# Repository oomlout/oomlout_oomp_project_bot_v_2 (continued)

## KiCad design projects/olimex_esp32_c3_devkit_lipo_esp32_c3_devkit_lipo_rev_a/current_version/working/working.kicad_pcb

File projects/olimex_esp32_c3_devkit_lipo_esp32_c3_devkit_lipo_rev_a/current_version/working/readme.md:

# esp32_c3_devkit_lipo
 
## summary 
* id: olimex_esp32_c3_devkit_lipo_esp32_c3_devkit_lipo_rev_a
* user: olimex
* name: esp32_c3_devkit_lipo
* board: esp32_c3_devkit_lipo_rev_a
* repo: https://github.com/OLIMEX/ESP32-C3-DevKit-Lipo
* src_file_repo_kicad_pcb: HARDWARE/ESP32-C3-DevKit-Lipo_Rev_A/ESP32-C3-DevKit-Lipo_Rev_A.kicad_pcb
* src_file_repo_kicad_pcb_link: https://github.com/OLIMEX/ESP32-C3-DevKit-Lipo/tree/main/HARDWARE/ESP32-C3-DevKit-Lipo_Rev_A/ESP32-C3-DevKit-Lipo_Rev_A.kicad_pcb

* src_file_repo_sch: HARDWARE/ESP32-C3-DevKit-Lipo_Rev_A/ESP32-C3-DevKit-Lipo_Rev_A.sch
* src_file_repo_sch_link: https://github.com/OLIMEX/ESP32-C3-DevKit-Lipo/tree/main/HARDWARE/ESP32-C3-DevKit-Lipo_Rev_A/ESP32-C3-DevKit-Lipo_Rev_A.sch
* full details link: https://github.com/oomlout/oomlout_oomp_project_bot_v_2/tree/main/projects/olimex_esp32_c3_devkit_lipo_esp32_c3_devkit_lipo_rev_a/current_version/working

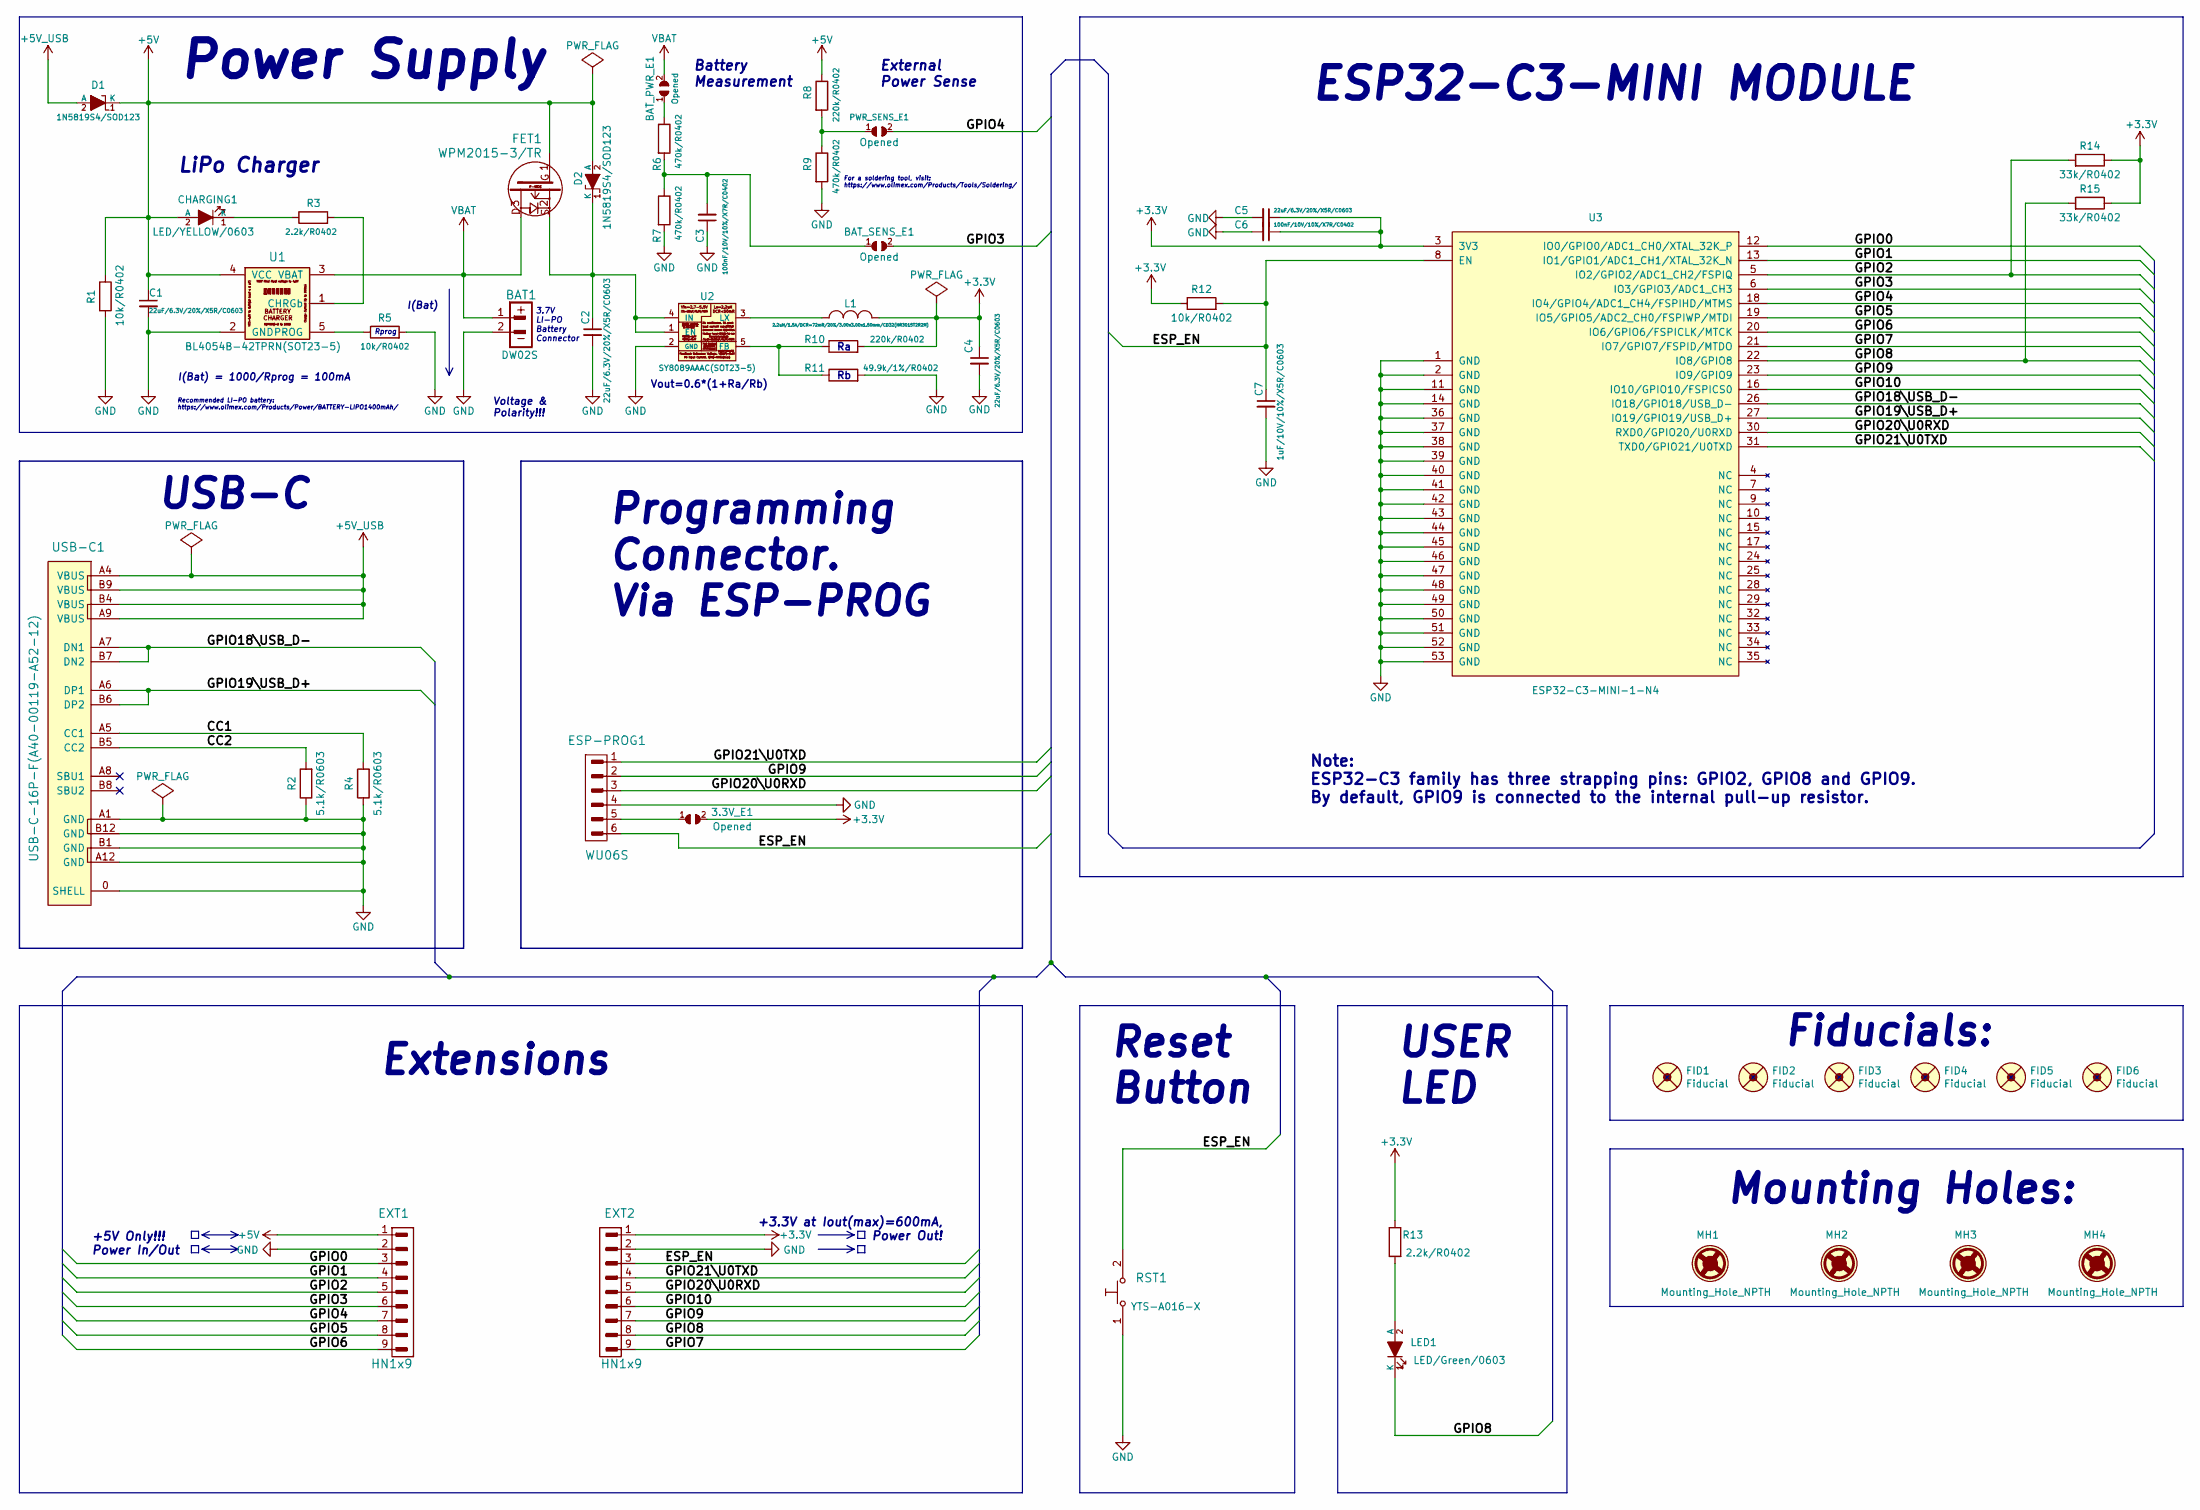
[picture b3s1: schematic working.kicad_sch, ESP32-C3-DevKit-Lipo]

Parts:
3.3V_E1: Opened; SJ_1_SMALLER
BAT1: DW02S; LIPO_BAT_VERTICAL_DW02S
BAT_PWR_E1: Opened; SJ_1_SMALLER
BAT_SENS_E1: Opened; SJ_1_SMALLER
C1, C2, C4, C5: 22uF/6.3V/20%/X5R/C0603; C_0603_5MIL_DWS
C3, C6: 100nF/10V/10%/X7R/C0402; C_0402_5MIL_DWS
C7: 1uF/10V/10%/X5R/C0603; C_0603_5MIL_DWS
CHARGING1: LED/YELLOW/0603; LED_0603_KA
D1, D2: 1N5819S4/SOD123; SOD-123_1C-2A_KA
ESP-PROG1: WU06S
EXT1, EXT2: HN1x9
FET1: WPM2015-3/TR; SOT23
FID1, FID2, FID3, FID4, FID5, FID6: Fiducial; Fiducial1x3
L1: 2.2uH/1.5A/DCR=72mR/20%/3.00x3.00x1.50mm/CD32(NR3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; CD32
LED1: LED/Green/0603; LED_0603_KA
MH1, MH2, MH3, MH4: Mounting_Hole_NPTH; Mounting_Hole_Drill-3.3mm_Clerance-7mm
PWR_SENS_E1: Opened; SJ_1_SMALLER
R1, R5, R12: 10k/R0402; R_0402_5MIL_DWS
R2, R4: 5.1k/R0603; R_0603_5MIL_DWS
R3, R13: 2.2k/R0402; R_0402_5MIL_DWS
R6, R7, R9: 470k/R0402; R_0402_5MIL_DWS
R8, R10: 220k/R0402; R_0402_5MIL_DWS
R11: 49.9k/1%/R0402; R_0402_5MIL_DWS
R14, R15: 33k/R0402; R_0402_5MIL_DWS
RST1: YTS-A016-X
U1: BL4054B-42TPRN(SOT23-5); SOT-23-5
U2: SY8089AAAC(SOT23-5); SOT-23-5
U3: ESP32-C3-MINI-1-N4; ESP32-­C3-­MINI­-1
USB-C1: USB-C-16P-F(A40-00119-A52-12); USB2.0_TYPE-C(A40-00119-A52-12)

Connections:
+3V3: 3.3V_E1.2, C4.1, C5.1, C6.1, EXT2.1, L1.2, R10.2, R12.1, R13.1, R14.1, R15.1, U3.3 (3V3)
+5V: C1.1, CHARGING1.2 (A), D1.1 (K), D2.2 (A), EXT1.1, FET1.1, R1.1, R8.1, U1.4 (VCC)
+5V_USB: D1.2 (A), USB-C1.A4 (VBUS), USB-C1.A9 (VBUS), USB-C1.B4 (VBUS), USB-C1.B9 (VBUS)
/CC1: R4.2, USB-C1.A5 (CC1)
/CC2: R2.2, USB-C1.B5 (CC2)
/ESP_EN: C7.1, ESP-PROG1.6, EXT2.3, R12.2, RST1.2, U3.8 (EN)
/GPIO0: EXT1.3, U3.12 (IO0/GPIO0/ADC1_CH0/XTAL_32K_P)
/GPIO1: EXT1.4, U3.13 (IO1/GPIO1/ADC1_CH1/XTAL_32K_N)
/GPIO2: EXT1.5, R14.2, U3.5 (IO2/GPIO2/ADC1_CH2/FSPIQ)
/GPIO3: BAT_SENS_E1.2, EXT1.6, U3.6 (IO3/GPIO3/ADC1_CH3)
/GPIO4: EXT1.7, PWR_SENS_E1.2, U3.18 (IO4/GPIO4/ADC1_CH4/FSPIHD/MTMS)
/GPIO5: EXT1.8, U3.19 (IO5/GPIO5/ADC2_CH0/FSPIWP/MTDI)
/GPIO6: EXT1.9, U3.20 (IO6/GPIO6/FSPICLK/MTCK)
/GPIO7: EXT2.9, U3.21 (IO7/GPIO7/FSPID/MTDO)
/GPIO8: EXT2.8, LED1.1 (K), R15.2, U3.22 (IO8/GPIO8)
/GPIO9: ESP-PROG1.2, EXT2.7, U3.23 (IO9/GPIO9)
/GPIO10: EXT2.6, U3.16 (IO10/GPIO10/FSPICS0)
/GPIO18\USB_D-: U3.26 (IO18/GPIO18/USB_D-), USB-C1.A7 (DN1), USB-C1.B7 (DN2)
/GPIO19\USB_D+: U3.27 (IO19/GPIO19/USB_D+), USB-C1.A6 (DP1), USB-C1.B6 (DP2)
/GPIO20\U0RXD: ESP-PROG1.3, EXT2.5, U3.30 (RXD0/GPIO20/U0RXD)
/GPIO21\U0TXD: ESP-PROG1.1, EXT2.4, U3.31 (TXD0/GPIO21/U0TXD)
GND: BAT1.2, C1.2, C2.2, C3.1, C4.2, C5.2, C6.2, C7.2, ESP-PROG1.4, EXT1.2, EXT2.2, R1.2, R2.1, R4.1, R5.2, R7.2, R9.2, R11.2, RST1.1, U1.2 (GND), U2.2 (GND), U3.1 (GND), U3.2 (GND), U3.11 (GND), U3.14 (GND), U3.36 (GND), U3.37 (GND), U3.38 (GND), U3.39 (GND), U3.40 (GND), U3.41 (GND), U3.42 (GND), U3.43 (GND), U3.44 (GND), U3.45 (GND), U3.46 (GND), U3.47 (GND), U3.48 (GND), U3.49 (GND), U3.50 (GND), U3.51 (GND), U3.52 (GND), U3.53 (GND), USB-C1.0 (SHELL), USB-C1.A1 (GND), USB-C1.A12 (GND), USB-C1.B1 (GND), USB-C1.B12 (GND)
unnamed: 3.3V_E1.1, ESP-PROG1.5
unnamed: BAT_PWR_E1.1, R6.1
unnamed: BAT_SENS_E1.1, C3.2, R6.2, R7.1
unnamed: C2.1, D2.1 (K), FET1.2, U2.1 (EN), U2.4 (IN)
unnamed: CHARGING1.1 (K), R3.1
unnamed: L1.1, U2.3 (LX)
unnamed: LED1.2 (A), R13.2
unnamed: PWR_SENS_E1.1, R8.2, R9.1
unnamed: R3.2, U1.1 (CHRGb)
unnamed: R5.1, U1.5 (PROG)
unnamed: R10.1, R11.1, U2.5 (FB)
VBAT: BAT1.1, BAT_PWR_E1.2, FET1.3, U1.3 (VBAT)

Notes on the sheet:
I(Bat)
Note: ESP32-C3 family has three strapping pins: GPIO2, GPIO8 and GPIO9. By default, GPIO9 is connected to the internal pull-up resistor.
Fiducials:
Battery Measurement
Power Supply
External Power Sense
LiPo Charger
Programming Connector. Via ESP-PROG
Mounting Holes:
+3.3V at Iout(max)=600mA, Power Out!
+5V Only!!! Power In/Out
Extensions
Reset Button
USER LED
ESP32-C3-MINI MODULE
Vout=0.6*(1+Ra/Rb)
Voltage & Polarity!!!
I(Bat) = 1000/Rprog = 100mA
Recommended LI-PO battery: https://www.olimex.com/Products/Power/BATTERY-LIPO1400mAh/
For a soldering tool, visit: https://www.olimex.com/Products/Tools/Soldering/
3.7V LI-PO Battery Connector
USB-C
Rprog

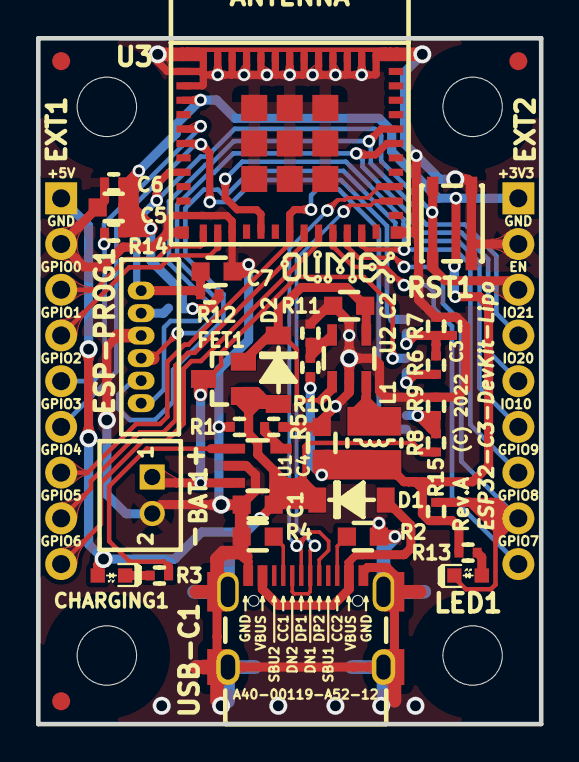
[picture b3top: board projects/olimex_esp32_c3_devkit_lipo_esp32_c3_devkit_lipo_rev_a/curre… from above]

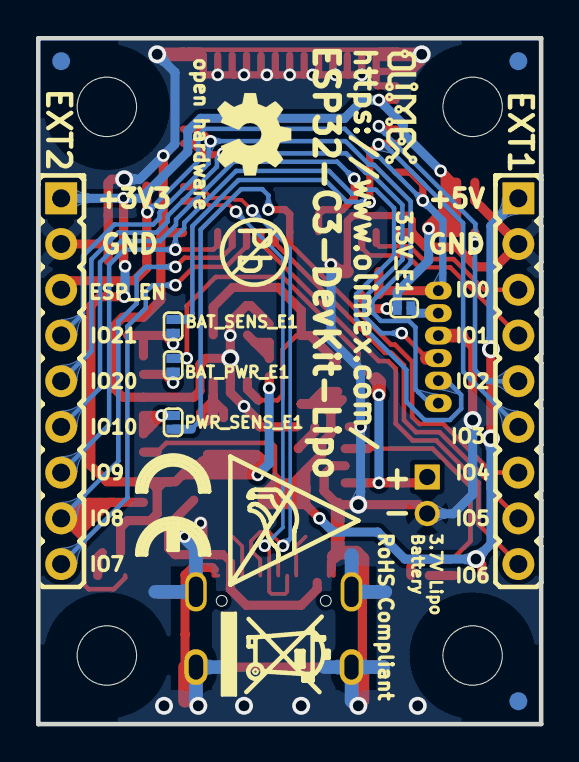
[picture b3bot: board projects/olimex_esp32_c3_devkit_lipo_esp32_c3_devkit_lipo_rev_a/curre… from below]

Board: 2 copper layers, 27.9 x 38.1 mm, 58 parts (15 on the bottom side), 34 nets.

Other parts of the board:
Logo_OLIMEX_1: Logo_OLIMEX_1; Logo_OLIMEX_80
Logo_OLIMEX_2: Logo_OLIMEX_2; Logo_OLIMEX_80
Sign_Antistatic: Sign_Antistatic
Sign_CE: CE_Sign
Sign_OSHW_7.3x6.0mm: Sign_OSHW_7.3x6.0mm; Sign_OSHW_7.3x6.0mmn
Sign_PB-Free: Sign_PB-Free
Sign_RecycleBin_1: Sign_RecycleBin_1

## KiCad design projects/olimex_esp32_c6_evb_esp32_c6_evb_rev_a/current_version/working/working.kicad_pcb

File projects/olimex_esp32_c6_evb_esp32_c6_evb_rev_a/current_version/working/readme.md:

# esp32_c6_evb
 
## summary 
* id: olimex_esp32_c6_evb_esp32_c6_evb_rev_a
* user: olimex
* name: esp32_c6_evb
* board: esp32_c6_evb_rev_a
* repo: https://github.com/OLIMEX/ESP32-C6-EVB
* src_file_repo_kicad_pcb: HARDWARE/Hardware-revision-A/ESP32-C6-EVB_Rev_A.kicad_pcb
* src_file_repo_kicad_pcb_link: https://github.com/OLIMEX/ESP32-C6-EVB/tree/main/HARDWARE/Hardware-revision-A/ESP32-C6-EVB_Rev_A.kicad_pcb

* src_file_repo_sch: HARDWARE/Hardware-revision-A/ESP32-C6-EVB_Rev_A.sch
* src_file_repo_sch_link: https://github.com/OLIMEX/ESP32-C6-EVB/tree/main/HARDWARE/Hardware-revision-A/ESP32-C6-EVB_Rev_A.sch
* full details link: https://github.com/oomlout/oomlout_oomp_project_bot_v_2/tree/main/projects/olimex_esp32_c6_evb_esp32_c6_evb_rev_a/current_version/working

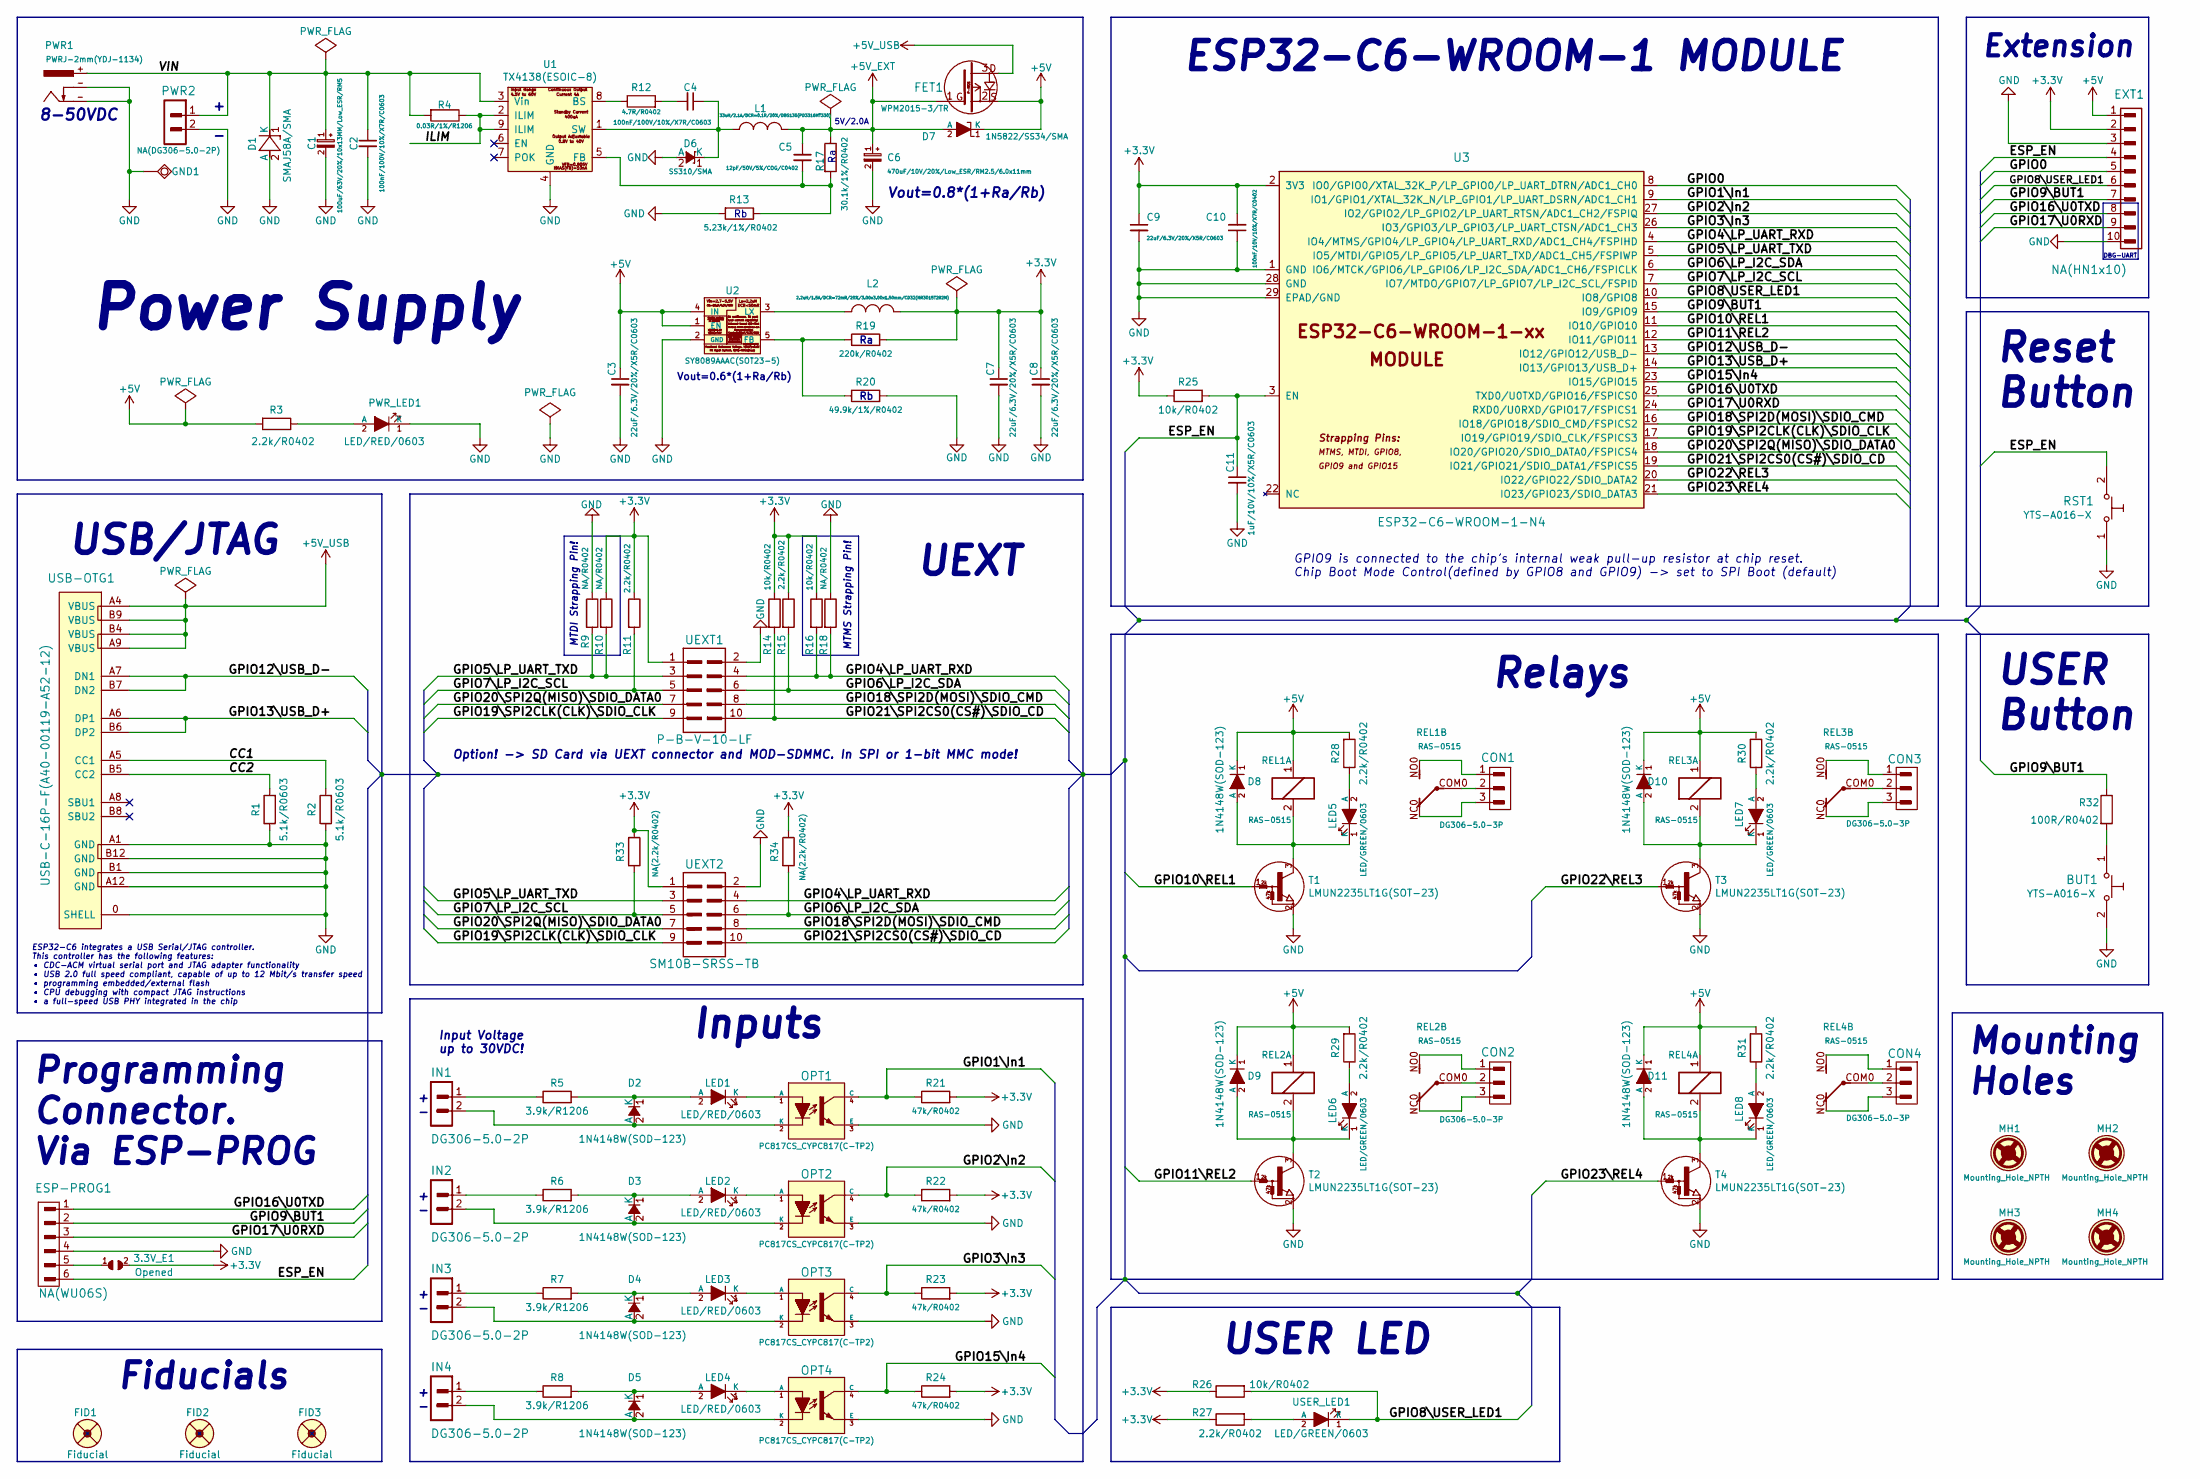
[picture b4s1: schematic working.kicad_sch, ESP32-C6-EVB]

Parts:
3.3V_E1: Opened; SJ_1_SMALLER
BUT1: YTS-A016-X
C1: 100uF/63V/20%/10x13MM/Low_ESR/RM5; CPOL-RM5mm_10.0x16.0mm_PTH
C2, C4: 100nF/100V/10%/X7R/C0603; C_0603_5MIL_DWS
C3, C7, C8, C9: 22uF/6.3V/20%/X5R/C0603; C_0603_5MIL_DWS
C5: 12pF/50V/5%/COG/C0402; C_0402_5MIL_DWS
C6: 470uF/10V/20%/Low_ESR/RM2.5/6.0x11mm; CPOL-RM2.5mm_6.3x11mm_PTH
C10: 100nF/10V/10%/X7R/C0402; C_0402_5MIL_DWS
C11: 1uF/10V/10%/X5R/C0603; C_0603_5MIL_DWS
CON1, CON2, CON3, CON4: DG306-5.0-3P; TB3-DG306-5.0_3P
D1: SMAJ58A/SMA; SMA-KA
D2, D3, D4, D5, D8, D9, D10, D11: 1N4148W(SOD-123); SOD-123_1C-2A_KA
D6: SS310/SMA; SMA-KA
D7: 1N5822/SS34/SMA; SMA-KA
ESP-PROG1: NA(WU06S); WU06S
EXT1: NA(HN1x10); HN1x10
FET1: WPM2015-3/TR; SOT23
FID1, FID2, FID3: Fiducial; Fiducial1x3
GND1: TESTPAD; TEST_PAD40x70_SQUARE
IN1, IN2, IN3, IN4: DG306-5.0-2P; TB2-DG306-5.0_2P
L1: 33uH/2.1A/DCR=0.1R/20%/DBS135(PD3316MT330); DBS135
L2: 2.2uH/1.5A/DCR=72mR/20%/3.00x3.00x1.50mm/CD32(NR3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; CD32
LED1, LED2, LED3, LED4: LED/RED/0603; LED_0603_KA
LED5, LED6, LED7, LED8: LED/GREEN/0603; LED_0603_KA
MH1, MH2, MH3, MH4: Mounting_Hole_NPTH; Mounting_Hole_Drill-3.3mm_Clerance-7mm
OPT1, OPT2, OPT3, OPT4: PC817CS_CYPC817(C-TP2); H11A817C_SMD(PC817X3NIP06)_FP
PWR1: PWRJ-2mm(YDJ-1134); PWRJ-2mm(YDJ-1136)
PWR2: NA(DG306-5.0-2P); TB2-DG306-5.0_2P
PWR_LED1: LED/RED/0603; LED_0603_KA
R1, R2: 5.1k/R0603; R_0603_5MIL_DWS
R3, R11, R15, R27, R28, R29, R30, R31: 2.2k/R0402; R_0402_5MIL_DWS
R4: 0.03R/1%/R1206; R_1206_5MIL_DWS
R5, R6, R7, R8: 3.9k/R1206; R_1206_5MIL_DWS
R9, R10, R18: NA/R0402; R_0402_5MIL_DWS
R12: 4.7R/R0402; R_0402_5MIL_DWS
R13: 5.23k/1%/R0402; R_0402_5MIL_DWS
R14, R16, R25, R26: 10k/R0402; R_0402_5MIL_DWS
R17: 30.1k/1%/R0402; R_0402_5MIL_DWS
R19: 220k/R0402; R_0402_5MIL_DWS
R20: 49.9k/1%/R0402; R_0402_5MIL_DWS
R21, R22, R23, R24: 47k/R0402; R_0402_5MIL_DWS
R32: 100R/R0402; R_0402_5MIL_DWS
R33, R34: NA(2.2k/R0402); R_0402_5MIL_DWS
REL1, REL2, REL3, REL4: RAS-0515; Relay_RAS-05-15
RST1: YTS-A016-X
T1, T2, T3, T4: LMUN2235LT1G(SOT-23); SOT23
U1: TX4138(ESOIC-8); ESOIC-8
U2: SY8089AAAC(SOT23-5); SOT-23-5
U3: ESP32-C6-WROOM-1-N4; ESP32-C6-WROOM-1-xx-UNIVERSAL_MODULE
UEXT1: P-B-V-10-LF; GBH-254-SMT-10
UEXT2: SM10B-SRSS-TB
USB-OTG1: USB-C-16P-F(A40-00119-A52-12); USB2.0_TYPE-C(A40-00119-A52-12)
USER_LED1: LED/GREEN/0603; LED_0603_KA

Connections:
+3.3V: 3.3V_E1.2, C7.1, C8.1, C9.1, C10.2, EXT1.2, L2.2, R10.1, R11.1, R14.1, R15.1, R16.1, R19.2, R21.2, R22.2, R23.2, R24.2, R25.1, R26.1, R27.1, R33.1, R34.1, U3.2 (3V3), UEXT1.1, UEXT2.1
+5V: C3.1, D7.1 (K), D8.1 (K), D9.1 (K), D10.1 (K), D11.1 (K), EXT1.1, FET1.2, R3.2, R28.2, R29.2, R30.2, R31.2, REL1.1, REL2.1, REL3.1, REL4.1, U2.1 (EN), U2.4 (IN)
+5V_EXT: C5.1, C6.1 (+), D7.2 (A), FET1.1, L1.2, R17.1
+5V_USB: FET1.3, USB-OTG1.A4 (VBUS), USB-OTG1.A9 (VBUS), USB-OTG1.B4 (VBUS), USB-OTG1.B9 (VBUS)
/CC1: R2.2, USB-OTG1.A5 (CC1)
/CC2: R1.2, USB-OTG1.B5 (CC2)
/ESP_EN: C11.1, ESP-PROG1.6, EXT1.4, R25.2, RST1.2, U3.3 (EN)
/GPIO0: EXT1.5, U3.8 (IO0/GPIO0/XTAL_32K_P/LP_GPIO0/LP_UART_D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)
/GPIO1\In1: OPT1.4 (C), R21.1, U3.9 (IO1/GPIO1/XTAL_32K_N/LP_GPIO1/LP_UART_D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)
/GPIO2\In2: OPT2.4 (C), R22.1, U3.27 (IO2/GPIO2/LP_GPIO2/LP_UART_RTSN/ADC1_CH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)
/GPIO3\In3: OPT3.4 (C), R23.1, U3.26 (IO3/GPIO3/LP_GPIO3/LP_UART_CTSN/ADC1_CH3)
/GPIO4\LP_UART_RXD: R16.2, R18.2, U3.4 (IO4/MTMS/GPIO4/LP_GPIO4/LP_UART_RXD/ADC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), UEXT1.4, UEXT2.4
/GPIO5\LP_UART_TXD: R9.2, R10.2, U3.5 (IO5/MTDI/GPIO5/LP_GPIO5/LP_UART_TXD/ADC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), UEXT1.3, UEXT2.3
/GPIO6\LP_I2C_SDA: R15.2, R34.2, U3.6 (IO6/MTCK/GPIO6/LP_GPIO6/LP_I2C_SDA/ADC1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), UEXT1.6, UEXT2.6
/GPIO7\LP_I2C_SCL: R11.2, R33.2, U3.7 (IO7/MTDO/GPIO7/LP_GPIO7/LP_I2C_SCL/FSPID), UEXT1.5, UEXT2.5
/GPIO8\USER_LED1: EXT1.6, R26.2, U3.10 (IO8/GPIO8), USER_LED1.1 (K)
/GPIO9\BUT1: ESP-PROG1.2, EXT1.7, R32.1, U3.15 (IO9/GPIO9)
/GPIO10\REL1: T1.1 (B), U3.11 (IO10/GPIO10)
/GPIO11\REL2: T2.1 (B), U3.12 (IO11/GPIO11)
/GPIO12\USB_D-: U3.13 (IO12/GPIO12/USB_D-), USB-OTG1.A7 (DN1), USB-OTG1.B7 (DN2)
/GPIO13\USB_D+: U3.14 (IO13/GPIO13/USB_D+), USB-OTG1.A6 (DP1), USB-OTG1.B6 (DP2)
/GPIO15\In4: OPT4.4 (C), R24.1, U3.23 (IO15/GPIO15)
/GPIO16\U0TXD: ESP-PROG1.1, EXT1.8, U3.25 (TXD0/U0TXD/GPIO16/FSPICS0)
/GPIO17\U0RXD: ESP-PROG1.3, EXT1.9, U3.24 (RXD0/U0RXD/GPIO17/FSPICS1)
/GPIO18\SPI2D(MOSI)\SDIO_CMD: U3.16 (IO18/GPIO18/SDIO_CMD/FSPICS2), UEXT1.8, UEXT2.8
/GPIO19\SPI2CLK(CLK)\SDIO_CLK: U3.17 (IO19/GPIO19/SDIO_CLK/FSPICS3), UEXT1.9, UEXT2.9
/GPIO20\SPI2Q(MISO)\SDIO_DATA0: U3.18 (IO20/GPIO20/SDIO_DATA0/FSPICS4), UEXT1.7, UEXT2.7
/GPIO21\SPI2CS0(CS#)\SDIO_CD: R14.2, U3.19 (IO21/GPIO21/SDIO_DATA1/FSPICS5), UEXT1.10, UEXT2.10
/GPIO22\REL3: T3.1 (B), U3.20 (IO22/GPIO22/SDIO_DATA2)
/GPIO23\REL4: T4.1 (B), U3.21 (IO23/GPIO23/SDIO_DATA3)
/ILIM: R4.1, U1.2 (ILIM), U1.9 (ILIM)
/VIN: C1.1 (+), C2.1, D1.1 (K), PWR1.+, PWR2.1, R4.2, U1.3 (Vin)
GND: BUT1.2, C1.2 (-), C2.2, C3.2, C6.2 (-), C7.2, C8.2, C9.2, C10.1, C11.2, D1.2 (A), D6.2 (A), ESP-PROG1.4, EXT1.3, EXT1.10, GND1.1, OPT1.3 (E), OPT2.3 (E), OPT3.3 (E), OPT4.3 (E), PWR1.-, PWR2.2, PWR_LED1.1 (K), R1.1, R2.1, R9.1, R13.2, R18.1, R20.2, RST1.1, T1.2 (E), T2.2 (E), T3.2 (E), T4.2 (E), U1.4 (GND), U2.2 (GND), U3.1 (GND), U3.28 (GND), U3.29 (EPAD/GND), UEXT1.2, UEXT2.2, USB-OTG1.0 (SHELL), USB-OTG1.A1 (GND), USB-OTG1.A12 (GND), USB-OTG1.B1 (GND), USB-OTG1.B12 (GND)
unnamed: 3.3V_E1.1, ESP-PROG1.5
unnamed: BUT1.1, R32.2
unnamed: C4.1, D6.1 (K), L1.1, U1.1 (SW)
unnamed: C4.2, R12.2
unnamed: C5.2, R13.1, R17.2, U1.5 (FB)
unnamed: CON1.1, REL1.NO0
unnamed: CON1.2, REL1.COM0
unnamed: CON1.3, REL1.NC0
unnamed: CON2.1, REL2.NO0
unnamed: CON2.2, REL2.COM0
unnamed: CON2.3, REL2.NC0
unnamed: CON3.1, REL3.NO0
unnamed: CON3.2, REL3.COM0
unnamed: CON3.3, REL3.NC0
unnamed: CON4.1, REL4.NO0
unnamed: CON4.2, REL4.COM0
unnamed: CON4.3, REL4.NC0
unnamed: D2.1 (K), LED1.2 (A), R5.2
unnamed: D2.2 (A), IN1.2, OPT1.2 (K)
unnamed: D3.1 (K), LED2.2 (A), R6.2
unnamed: D3.2 (A), IN2.2, OPT2.2 (K)
unnamed: D4.1 (K), LED3.2 (A), R7.2
unnamed: D4.2 (A), IN3.2, OPT3.2 (K)
unnamed: D5.1 (K), LED4.2 (A), R8.2
unnamed: D5.2 (A), IN4.2, OPT4.2 (K)
unnamed: D8.2 (A), LED5.1 (K), REL1.2, T1.3 (C)
unnamed: D9.2 (A), LED6.1 (K), REL2.2, T2.3 (C)
unnamed: D10.2 (A), LED7.1 (K), REL3.2, T3.3 (C)
unnamed: D11.2 (A), LED8.1 (K), REL4.2, T4.3 (C)
unnamed: IN1.1, R5.1
unnamed: IN2.1, R6.1
unnamed: IN3.1, R7.1
unnamed: IN4.1, R8.1
unnamed: L2.1, U2.3 (LX)
unnamed: LED1.1 (K), OPT1.1 (A)
unnamed: LED2.1 (K), OPT2.1 (A)
unnamed: LED3.1 (K), OPT3.1 (A)
unnamed: LED4.1 (K), OPT4.1 (A)
unnamed: LED5.2 (A), R28.1
unnamed: LED6.2 (A), R29.1
unnamed: LED7.2 (A), R30.1
unnamed: LED8.2 (A), R31.1
unnamed: PWR_LED1.2 (A), R3.1
unnamed: R12.1, U1.8 (BS)
unnamed: R19.1, R20.1, U2.5 (FB)
unnamed: R27.2, USER_LED1.2 (A)

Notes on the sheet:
MTMS Strapping Pin!
Reset Button
Power Supply
Input Voltage up to 30VDC!
Relays
GPIO9 is connected to the chip’s internal weak pull-up resistor at chip reset. Chip Boot Mode Control(defined by GPIO8 and GPIO9) -> set to SPI Boot (default)
USER Button
5V/2.0A
UEXT
Extension
Inputs
8-50VDC
Vout=0.8*(1+Ra/Rb)
USB/JTAG
Vout=0.6*(1+Ra/Rb)
Fiducials
USER LED
DBG-UART
ESP32-C6 integrates a USB Serial/JTAG controller. This controller has the following features: • CDC-ACM virtual serial port and JTAG adapter functionality • USB 2.0 full speed compliant, capable of up to 12 Mbit/s transfer speed • programming embedded/external flash • CPU debugging with compact JTA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
Programming Connector. Via ESP-PROG
ESP32-C6-WROOM-1 MODULE
Mounting Holes
Option! -> SD Card via UEXT connector and MOD-SDMMC. In SPI or 1-bit MMC mode!
MTDI Strapping Pin!

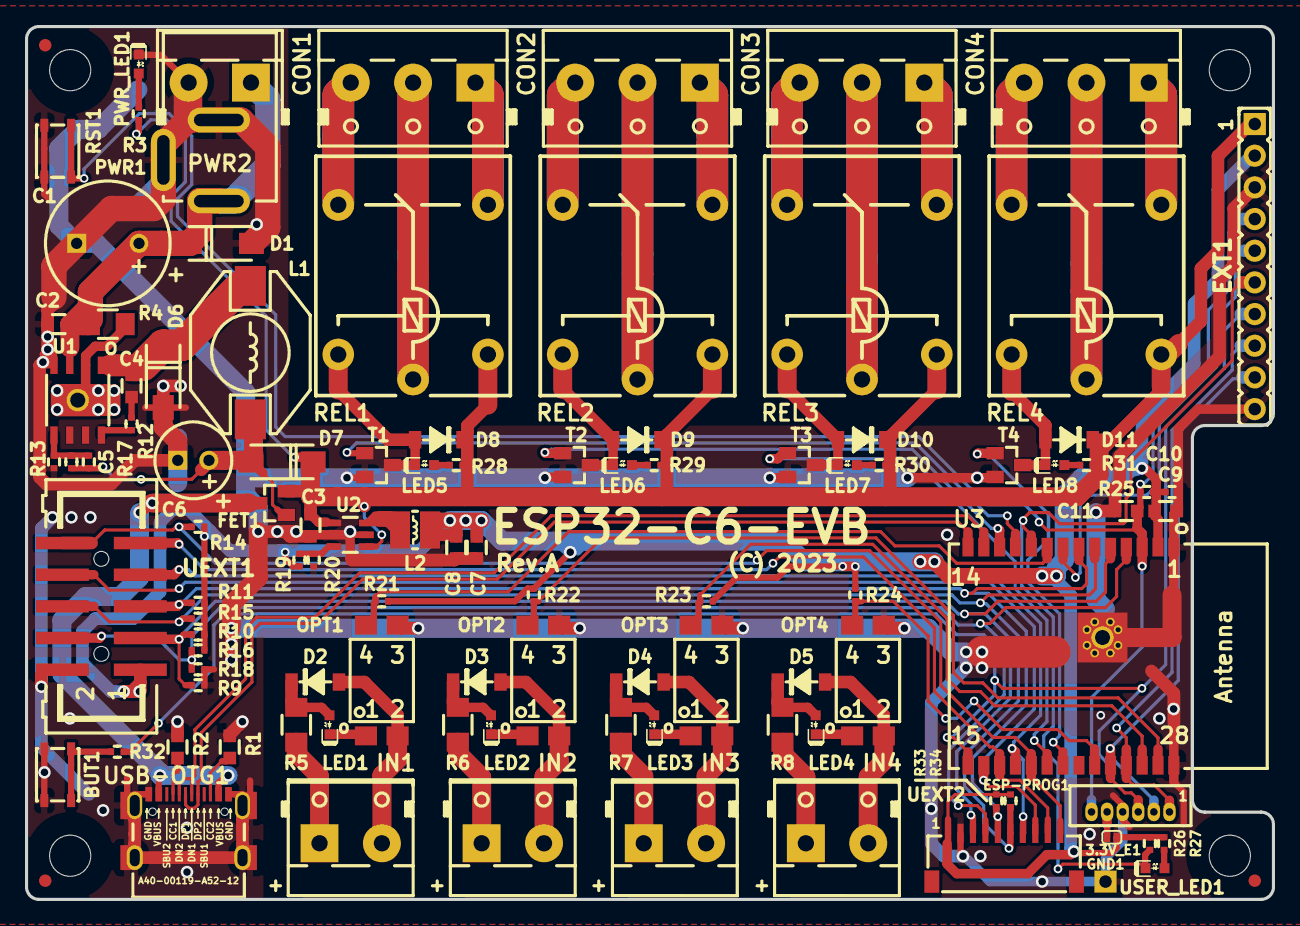
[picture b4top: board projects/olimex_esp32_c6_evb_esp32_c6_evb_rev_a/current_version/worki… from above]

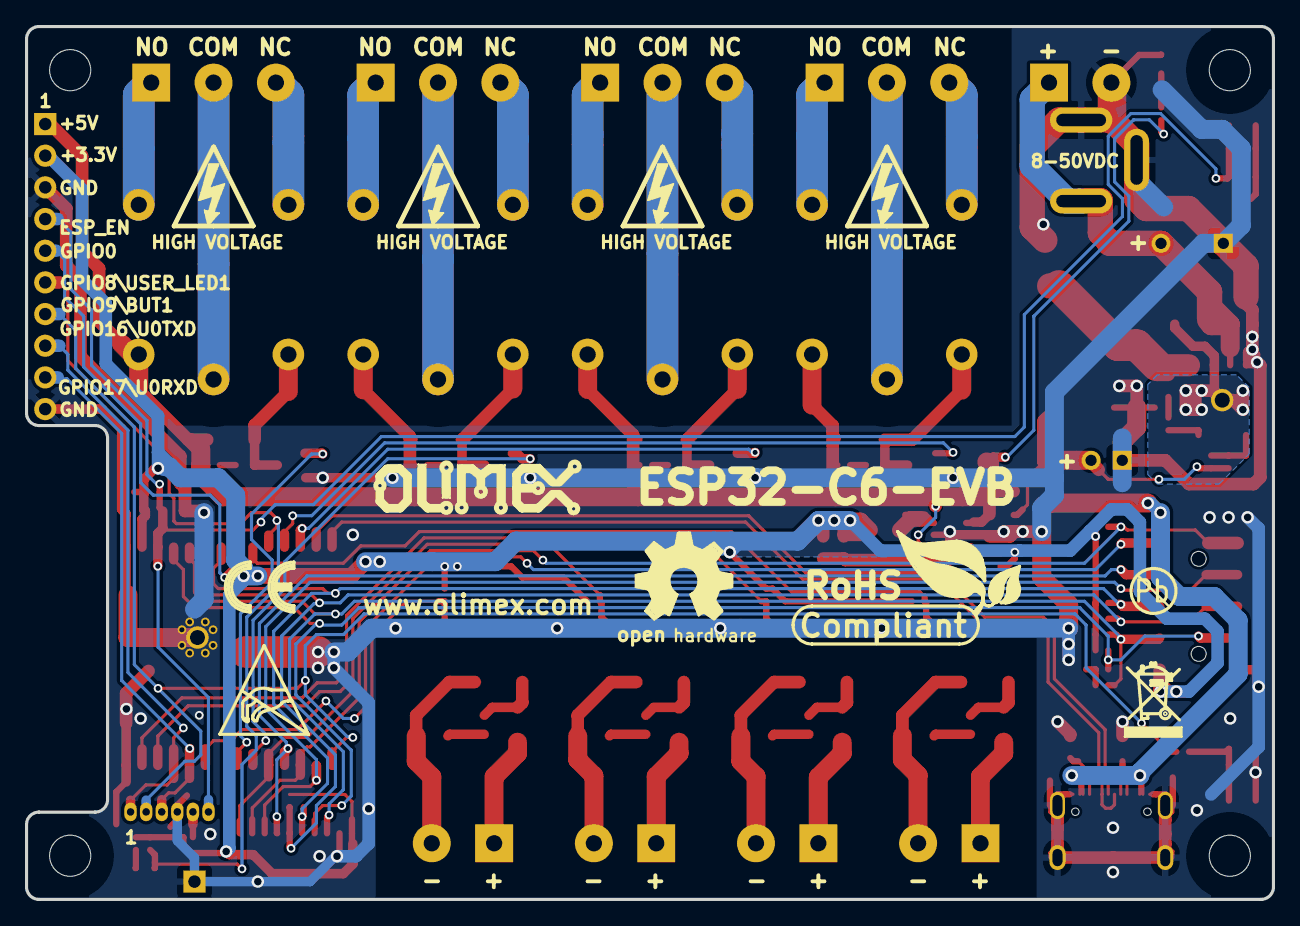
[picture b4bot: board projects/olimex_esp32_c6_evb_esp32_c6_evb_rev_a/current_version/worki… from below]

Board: 2 copper layers, 100.0 x 70.0 mm, 121 parts (11 on the bottom side), 79 nets.

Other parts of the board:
Logo_OLIMEX_TB: Logo_OLIMEX_TB
Sign_Antistatic: Sign_Antistatic
Sign_CE: CE_Sign
Sign_High_Voltage: Sign_High_Voltage
Sign_High_Voltage#2, Sign_High_Voltage#3, Sign_High_Voltage#4: Sign_High_Voltage
Sign_OSHW_8x8: Sign_OSHW_8x8
Sign_PB-Free: Sign_PB-Free
Sign_RecycleBin_1: Sign_RecycleBin_1
Sign_RoHS_1: Sign_RoHS_1
